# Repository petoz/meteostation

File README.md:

# meteostation
build on Raspberry Pi and arduino

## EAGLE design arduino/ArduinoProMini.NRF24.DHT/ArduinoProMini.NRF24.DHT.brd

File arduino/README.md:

This directory is for arduino part of meteostation

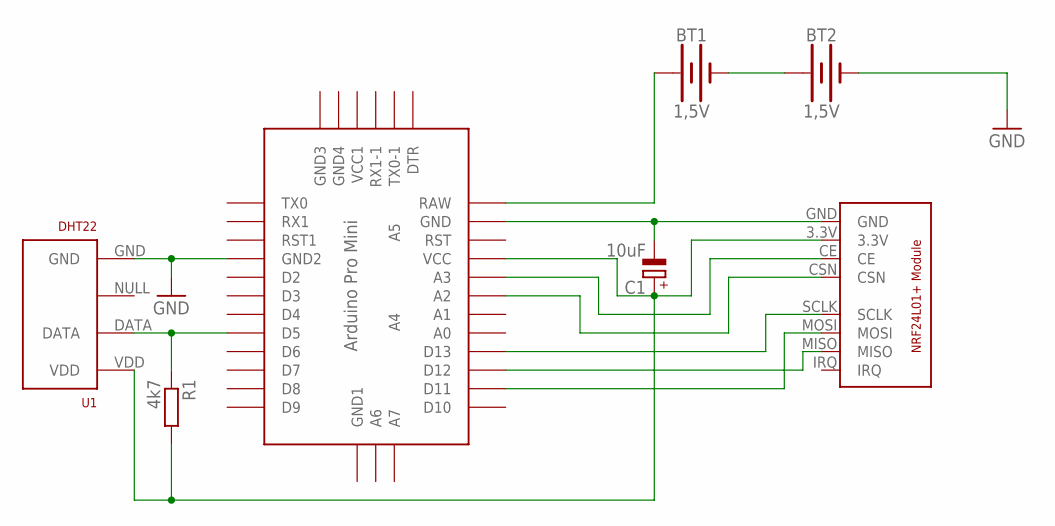
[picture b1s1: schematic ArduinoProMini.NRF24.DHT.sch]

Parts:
BT1, BT2: 1,5V; BATTERY-AA
C1: 10uF; E2-5
R1: 4k7; 0204/7
U1: DHT22; RHT03_DHT-22/RA
U$1: ABK-PRO-MINI
U$2: NRF24L01+MODULE

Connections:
3.3V: C1.+, R1.2, U1.VDD, U$1.VCC, U$2.3.3V
GND: BT2.GND@1 (-), C1.-, U1.GND, U$1.GND, U$1.GND1 (GND2), U$2.GND
unnamed: BT1.GND@1 (-), BT2.PWR@1 (+)
unnamed: R1.1, U1.DATA, U$1.D5
unnamed: U$1.A3, U$2.CE
unnamed: U$1.A2, U$2.CSN
unnamed: U$1.D13, U$2.SCLK
unnamed: U$1.D11, U$2.MOSI
unnamed: U$1.D12, U$2.MISO
RAW: BT1.PWR@1 (+), U$1.RAW

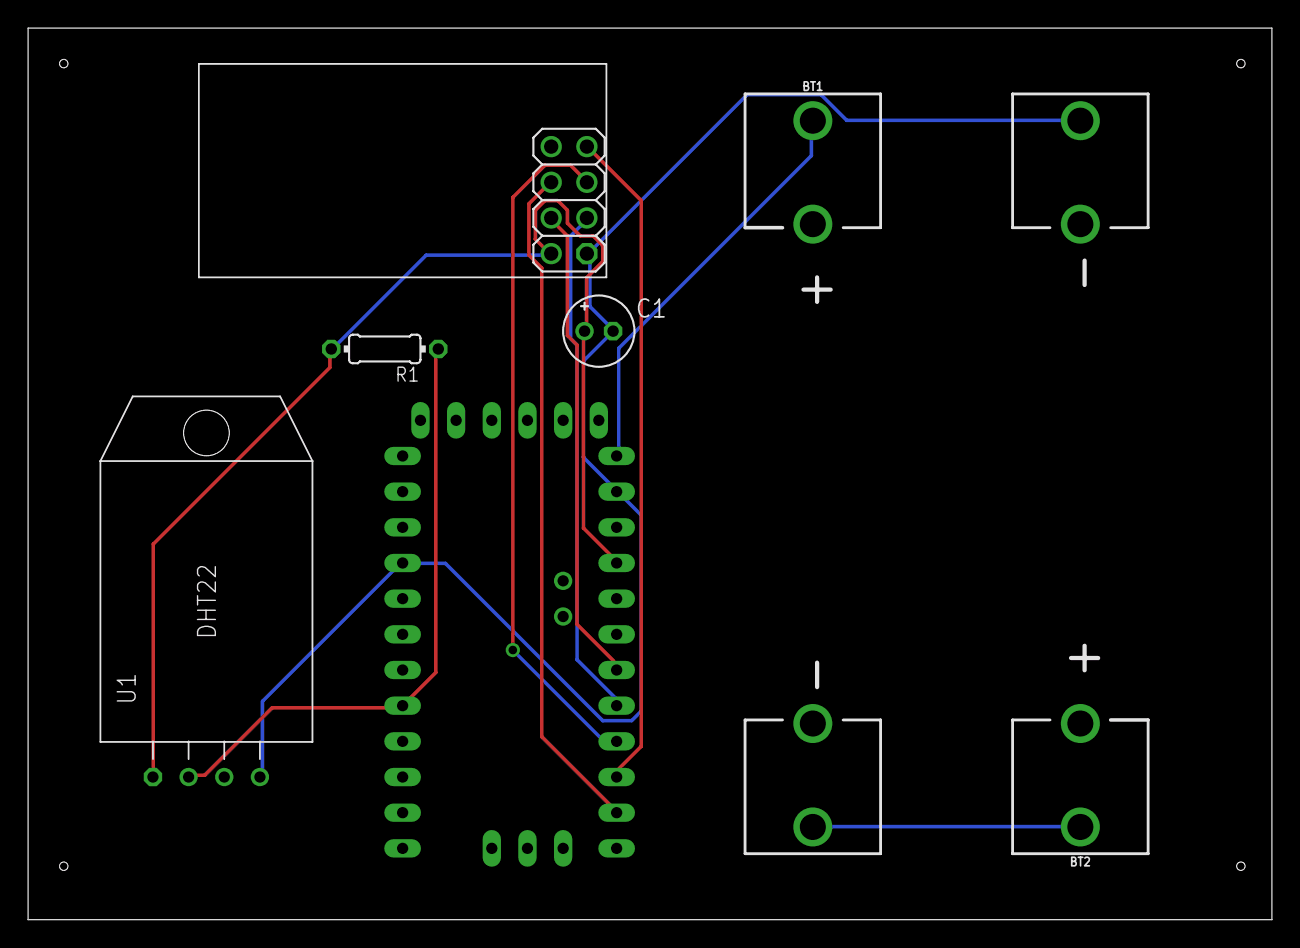
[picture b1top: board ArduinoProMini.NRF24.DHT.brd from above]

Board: 2 copper layers, 88.6 x 63.5 mm, 7 parts (0 on the bottom side), 10 nets.

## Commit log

2018-02-15 added python script sensor.api.py for reading rasperry sensors and uploading data to meteotemplate
2018-02-15 read data from nRF24 arduino sensors
2018-02-15 added README.md
2018-02-15 added compile script
2018-02-15 add rc.local link
2018-02-15 edit
2018-02-15 remove sleep(1) line from .cpp
2018-02-15 added arduino dircetory
2018-02-15 added code for arduino transmitter
2018-02-15 Description
2018-02-15 test for git
2018-02-15 change file name
2018-02-15 deleted file
2018-02-15 iremoved test files
2018-02-15 modified readme.md
2018-02-15 edit \br
2018-02-15 arduino transmitter board - eagle files
2018-02-20 string subst
2018-02-21 esp display station
2018-02-21 rename to wemos.display.station
2018-02-21 deleted old files
2018-02-21 wifi change
2018-02-23 convert string to float, display repetedly t/h
2018-05-10 added UNIX timestemp to string
2018-05-10 split every sensor update to different update
2018-05-10 syntax
2018-05-10 error
2018-05-10 passwd added
2018-05-10 revert changes, added devel branch
2018-05-10 every sensor has own update
2018-05-10 zczc
2018-05-11 test new
2018-05-11 error in file namewq
2018-05-11 standalone program for reading internal sensors
2018-05-11 standalone program for internal sensors
2018-05-14 added compiled file to git
2018-05-14 internal sens
2018-05-15 create file for in sensors
2018-05-15 no int. sensors
2018-05-15 read Internal sernsors from file
2018-05-15 remove "get internal sensors" part of programm
2018-05-15 remove part "read internal sensors"
2018-05-15 remove unnecesarry code
2018-05-15 clean code, alll sensors from external files
2018-05-15 renamed to better describe
2018-05-16 try not to remove files aftre update
2018-05-16 files needs to be removed
2018-07-16 added 4-th sensor
2018-07-16 added 4-th sensor 2
2018-07-16 remove added lines
2018-07-17 modified bat sensor as NO2_x sensor
2018-07-17 move outfile instead of remove to watch last values
2018-07-20 update code to tabs
2018-07-23 tabbed source
2018-07-23 modified source to tabs
2018-07-23 test atom
2018-08-06 on test sample temp; new 5-th sensor
2018-08-06 added 5-th sensor
2018-08-07 5-th sensor
2018-08-07 changed T5 to LT1
2018-08-07 co2 to co
2018-08-09 simplify and orginize code
2018-08-09 added very simple checksum to eliminate errors for wireless sensor
2018-08-09 definition of new variables
2018-08-09 mod to checksum sensor 4
2018-08-09 modified to checksum sensor 3
2018-08-09 sensor 3 power to low
2018-08-10 all sensors with simple checksum
2018-08-22 add shutdown function for low battery
2018-08-23 add "shutdown" function for battery
2018-08-23 added "shutdown" function
2018-08-28 low voltage "shutdown"
2018-09-29 added schematic + board
2018-10-03 Add files via upload
    voltage monitor
2023-02-09 zmena url ?
2023-02-09 add new python codes

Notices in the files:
parts and their libraries:
SparkFun-Batteries: Licensing: Creative Commons ShareAlike 4.0 International - https://creativecommons.org/licenses/by-sa/4.0
